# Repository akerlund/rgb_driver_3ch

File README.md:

# LED driver PCB, 3ch RGB

STM32F100 microcontroller with small SOT23 MOSFETs to drive 12V LED strips.
Four LEDs and two buttons for custom use.
Three potentiometers for controlling the light; HSL, i.e., Hue, Saturation and Light.
A CP2102 serial to USB interface.
Pinout for other peripherals, i.e., I2C, SPI and UART.

## Build

Using the ARM compiler (arm-none-eabi), which can be installed with

```
sudo apt-get install gcc-arm-none-eabi
```
then change directory and run the make file
```
cd code
make
```

## Program
I use Devilholk's verion of [stm32flash](https://github.com/devilholk/stm32flash),
with a cheap CP2102 USB to UART Bridge Controller.

### Programming sequence example

```
~/rgb_driver_3ch$ stm32flash -b 115200 -Rcs.rts -Bcs.dtr -w code/build/driver_rgb_3ch.bin /dev/ttyUSB0
stm32flash - http://stm32flash.googlecode.com/

Using Parser : Raw BINARY
Serial Config: 115200 8E1
Version      : 0x22
Option 1     : 0x00
Option 2     : 0x00
Device ID    : 0x0420 (Medium-density VL)
RAM          : 8KiB  (512b reserved by bootloader)
Flash        : 128KiB (sector size: 4x1024)
Option RAM   : 15b
System RAM   : 2KiB

Wrote address 0x08003304 (100.00%) Done.
```

### Pin configurations
Make sure you connect cables like this;

PCB | CP2102
-- | --
3.3V | N/C
GND | GND
TX | RXI
RX | TXO
RESET | RTS
BOOT | DTR

If you haven't, remember to add your username to the dialout group

```
sudo adduser <user_name> dialout
```

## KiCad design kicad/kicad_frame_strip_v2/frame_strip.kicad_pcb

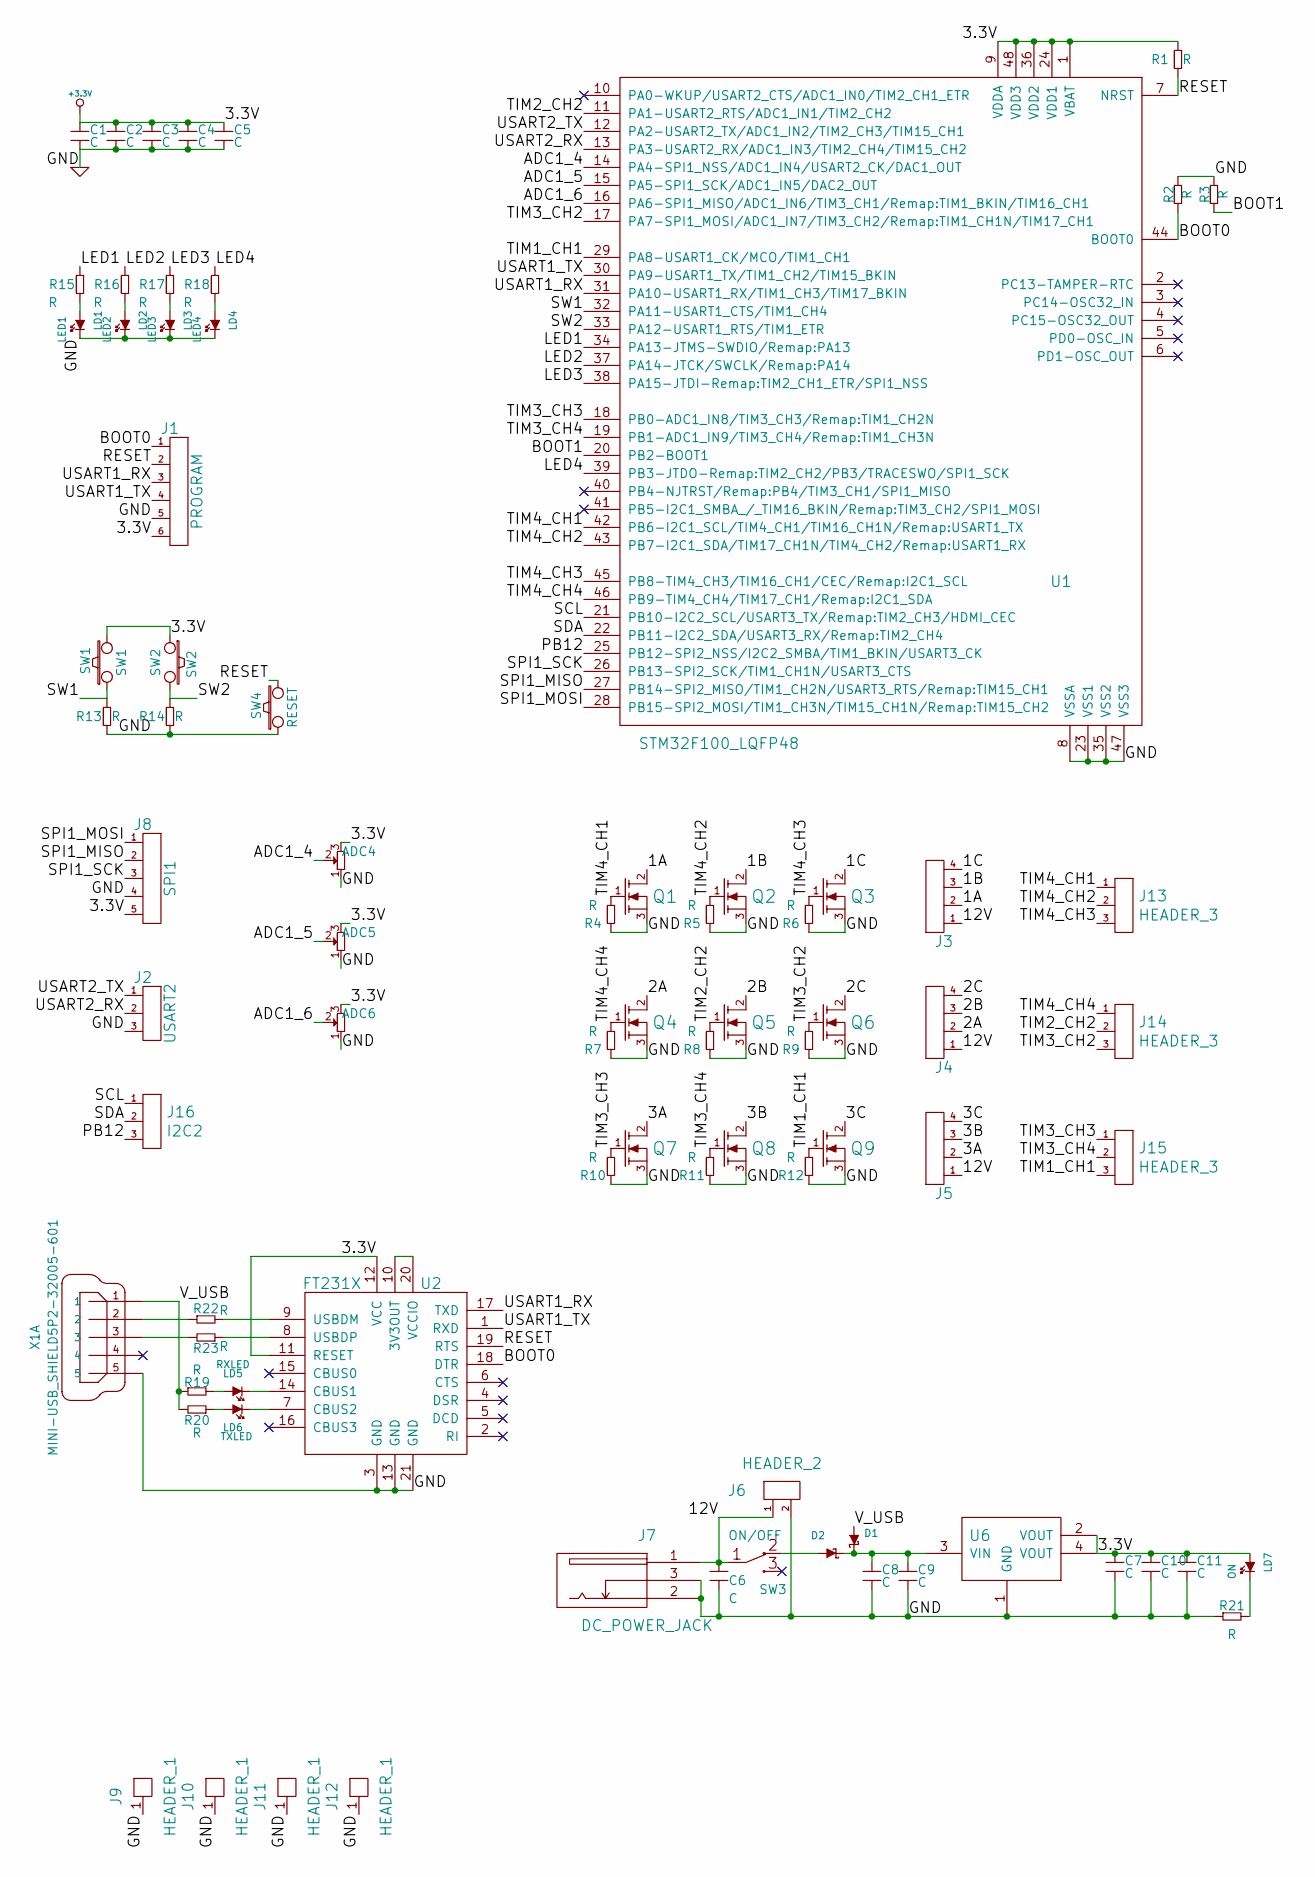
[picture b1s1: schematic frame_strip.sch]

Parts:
ADC4, ADC5, ADC6: POT; pin_socket_3
C1, C2, C3, C4, C5, C7, C8, C9, C10, C11: C; c_0603
C6: C; c_elec_5x5.3
D1, D2: SCHOTTKY; sod123
J1: PROGRAM; pin_strip_6
J2: USART2; pin_strip_3
J3, J4, J5: HEADER_4; pin_strip_4
J6: HEADER_2; pin_socket_2
J7: DC_POWER_JACK; dc_socket
J8: SPI1; pin_strip_5
J9, J10, J11, J12: HEADER_1; drill_2.0mm
J13, J14, J15: HEADER_3; pin_socket_3
J16: I2C2; pin_socket_3
LD1: LED1; Led_0805
LD2: LED2; Led_0805
LD3: LED3; Led_0805
LD4: LED4; Led_0805
LD5: RXLED; Led_0805
LD6: TXLED; Led_0805
LD7: ON; Led_0805
Q1, Q2, Q3, Q4, Q5, Q6, Q7, Q8, Q9: MOS_N_GDS; sot23
R1, R2, R3, R4, R5, R6, R7, R8, R9, R10, R11, R12, R13, R14, R15, R16, R17, R18, R19, R20, R21, R22, R23: R; r_0603
SW1: SW1; smd_push
SW2: SW2; smd_push
SW3: ON/OFF; switch_mmp122-r
SW4: RESET; smd_push
U1: STM32F100_LQFP48; lqfp48
U2: FT231X; qfn-20
U6: sot223
X1: MINI-USB_SHIELD5P2-32005-601; conn_usb_B_mini_smd

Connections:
+3.3V: ADC4.3, ADC5.3, ADC6.3, C1.1, C2.1, C3.1, C4.1, C5.1, C7.1, C10.1, C11.1, J1.6, J8.5, LD7.1 (A), R1.1, SW1.2, SW2.1, U1.1 (VBAT), U1.9 (VDDA), U1.24 (VDD1), U1.36 (VDD2), U1.48 (VDD3), U2.11 (RESET), U2.12 (VCC), U6.2 (VOUT), U6.4 (VOUT)
/1A: J3.2, Q1.2 (D)
/1B: J3.3, Q2.2 (D)
/1C: J3.4, Q3.2 (D)
/2A: J4.2, Q4.2 (D)
/2B: J4.3, Q5.2 (D)
/2C: J4.4, Q6.2 (D)
/3A: J5.2, Q7.2 (D)
/3B: J5.3, Q8.2 (D)
/3C: J5.4, Q9.2 (D)
/12V: C6.1, J3.1, J4.1, J5.1, J6.1, J7.1, SW3.1 (COM)
/ADC1_4: ADC4.2, U1.14 (PA4-SPI1_NSS/ADC1_IN4/USART2_CK/DAC1_OUT)
/ADC1_5: ADC5.2, U1.15 (PA5-SPI1_SCK/ADC1_IN5/DAC2_OUT)
/ADC1_6: ADC6.2, U1.16 (PA6-SPI1_MISO/ADC1_IN6/TIM3_CH1/Remap:T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)
/BOOT0: J1.1, R2.2, U1.44 (BOOT0), U2.18 (DTR)
/BOOT1: R3.2, U1.20 (PB2-BOOT1)
/LED1: R15.1, U1.34 (PA13-JTMS-SWDIO/Remap:PA13)
/LED2: R16.1, U1.37 (PA14-JTCK/SWCLK/Remap:PA14)
/LED3: R17.1, U1.38 (PA15-JTDI-Remap:TIM2_CH1_ETR/SPI1_NSS)
/LED4: R18.1, U1.39 (PB3-JTDO-Remap:TIM2_CH2/PB3/TRACESWO/SP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)
/PB12: J16.3, U1.25 (PB12-SPI2_NSS/I2C2_SMBA/TIM1_BKIN/USART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)
/RESET: J1.2, R1.2, SW4.2, U1.7 (NRST), U2.19 (RTS)
/SCL: J16.1, U1.21 (PB10-I2C2_SCL/USART3_TX/Remap:TIM2_CH3/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)
/SDA: J16.2, U1.22 (PB11-I2C2_SDA/USART3_RX/Remap:TIM2_CH4)
/SPI1_MISO: J8.2, U1.27 (PB14-SPI2_MISO/TIM1_CH2N/USART3_RTS/Rem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)
/SPI1_MOSI: J8.1, U1.28 (PB15-SPI2_MOSI/TIM1_CH3N/TIM15_CH1N/Rem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)
/SPI1_SCK: J8.3, U1.26 (PB13-SPI2_SCK/TIM1_CH1N/USART3_CTS)
/SW1: R13.1, SW1.1, U1.32 (PA11-USART1_CTS/TIM1_CH4)
/SW2: R14.1, SW2.2, U1.33 (PA12-USART1_RTS/TIM1_ETR)
/TIM1_CH1: J15.3, Q9.1 (G), R12.1, U1.29 (PA8-USART1_CK/MCO/TIM1_CH1)
/TIM2_CH2: J14.2, Q5.1 (G), R8.1, U1.11 (PA1-USART2_RTS/ADC1_IN1/TIM2_CH2)
/TIM3_CH2: J14.3, Q6.1 (G), R9.1, U1.17 (PA7-SPI1_MOSI/ADC1_IN7/TIM3_CH2/Remap:T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)
/TIM3_CH3: J15.1, Q7.1 (G), R10.1, U1.18 (PB0-ADC1_IN8/TIM3_CH3/Remap:TIM1_CH2N)
/TIM3_CH4: J15.2, Q8.1 (G), R11.1, U1.19 (PB1-ADC1_IN9/TIM3_CH4/Remap:TIM1_CH3N)
/TIM4_CH1: J13.1, Q1.1 (G), R4.1, U1.42 (PB6-I2C1_SCL/TIM4_CH1/TIM16_CH1N/Remap: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)
/TIM4_CH2: J13.2, Q2.1 (G), R5.1, U1.43 (PB7-I2C1_SDA/TIM17_CH1N/TIM4_CH2/Remap: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)
/TIM4_CH3: J13.3, Q3.1 (G), R6.1, U1.45 (PB8-TIM4_CH3/TIM16_CH1/CEC/Remap:I2C1_S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)
/TIM4_CH4: J14.1, Q4.1 (G), R7.1, U1.46 (PB9-TIM4_CH4/TIM17_CH1/Remap:I2C1_SDA)
/USART1_RX: J1.3, U1.31 (PA10-USART1_RX/TIM1_CH3/TIM17_BKIN), U2.17 (TXD)
/USART1_TX: J1.4, U1.30 (PA9-USART1_TX/TIM1_CH2/TIM15_BKIN), U2.1 (RXD)
/USART2_RX: J2.2, U1.13 (PA3-USART2_RX/ADC1_IN3/TIM2_CH4/TIM15_C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)
/USART2_TX: J2.1, U1.12 (PA2-USART2_TX/ADC1_IN2/TIM2_CH3/TIM15_C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)
/V_USB: D1.1 (A), R19.1, R20.2, X1.1
GND: ADC4.1, ADC5.1, ADC6.1, C1.2, C2.2, C3.2, C4.2, C5.2, C6.2, C7.2, C8.2, C9.2, C10.2, C11.2, J1.5, J2.3, J6.2, J7.2, J7.3, J8.4, J9.1, J10.1, J11.1, J12.1, LD1.2 (K), LD2.2 (K), LD3.2 (K), LD4.2 (K), Q1.3 (S), Q2.3 (S), Q3.3 (S), Q4.3 (S), Q5.3 (S), Q6.3 (S), Q7.3 (S), Q8.3 (S), Q9.3 (S), R2.1, R3.1, R4.2, R5.2, R6.2, R7.2, R8.2, R9.2, R10.2, R11.2, R12.2, R13.2, R14.2, R21.1, SW4.1, U1.8 (VSSA), U1.23 (VSS1), U1.35 (VSS2), U1.47 (VSS3), U2.3 (GND), U2.13 (GND), U2.21 (GND), U6.1 (GND), X1.5
unnamed: C8.1, C9.1, D1.2 (K), D2.2 (K), U6.3 (VIN)
unnamed: D2.1 (A), SW3.2 (NC)
unnamed: LD1.1 (A), R15.2
unnamed: LD2.1 (A), R16.2
unnamed: LD3.1 (A), R17.2
unnamed: LD4.1 (A), R18.2
unnamed: LD5.1 (A), R19.2
unnamed: LD5.2 (K), U2.14 (CBUS1)
unnamed: LD6.1 (A), R20.1
unnamed: LD6.2 (K), U2.7 (CBUS2)
unnamed: LD7.2 (K), R21.2
unnamed: R22.1, X1.2
unnamed: R22.2, U2.9 (USBDM)
unnamed: R23.1, U2.8 (USBDP)
unnamed: R23.2, X1.3
unnamed: U2.10 (3V3OUT), U2.20 (VCCIO)

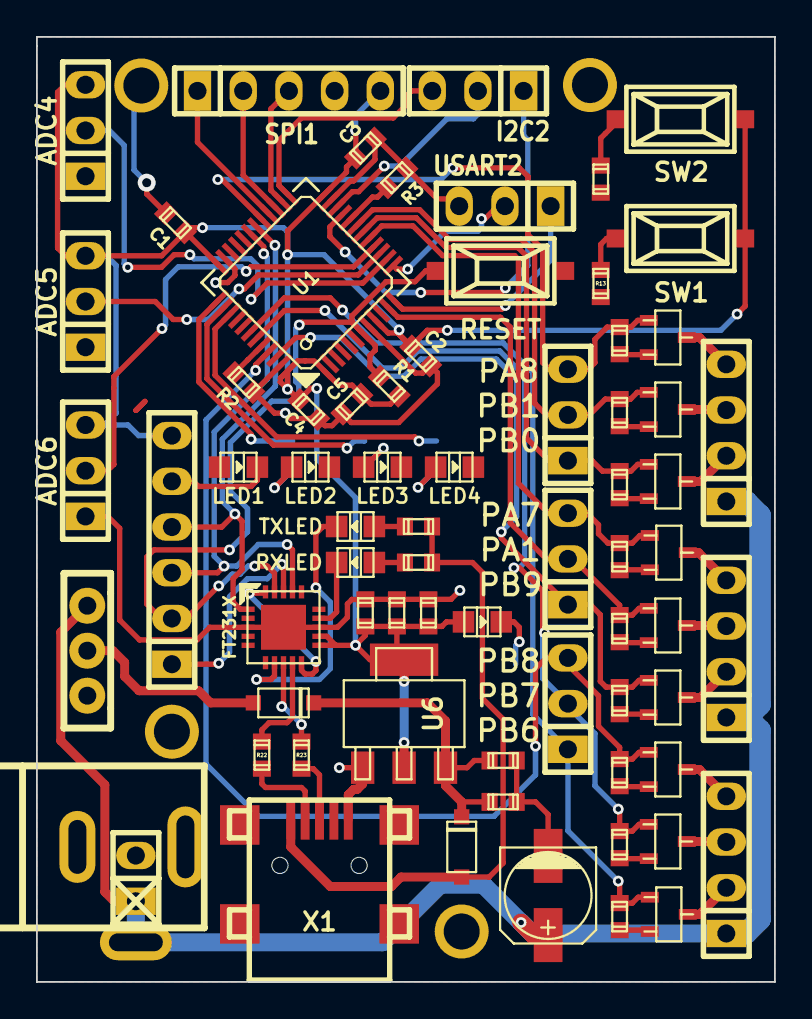
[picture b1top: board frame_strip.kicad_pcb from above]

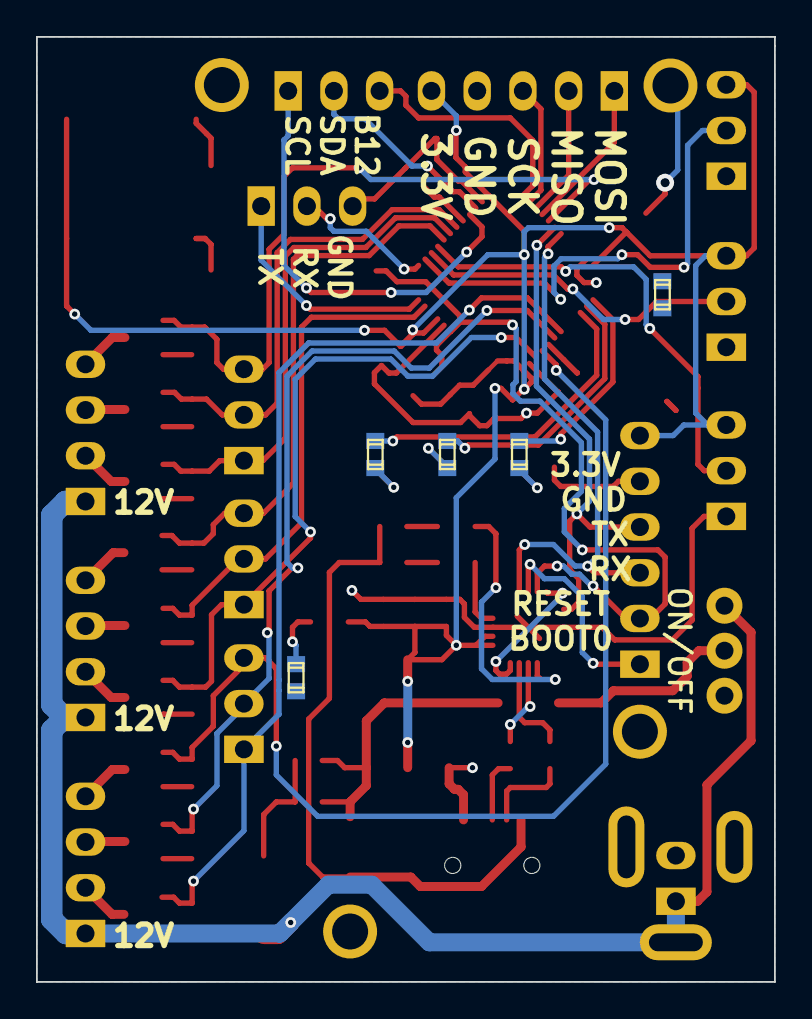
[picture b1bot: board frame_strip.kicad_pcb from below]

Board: 2 copper layers, 41.0 x 52.5 mm, 79 parts (5 on the bottom side), 60 nets.

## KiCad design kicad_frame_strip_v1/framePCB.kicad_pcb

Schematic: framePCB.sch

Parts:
C1: C; c_elec_8x6.5
C2, C4, C5, C6, C7: C; c_0603
D1: SETTING; Led_0603
D2: 1; Led_0603
D3: 3; Led_0603
D4, D5: 2; Led_0603
D6: 4; Led_0603
J1: dc_jack; dc_socket
J2: BOOT; smd_pin_5
J3: VIN/GRB0; smd_pin_4
J4: VIN/GRB1; smd_pin_4
J5: VIN/RGB2; smd_pin_4
J6: USART; smd_pin_3
J7: JST; pin_strip_2
J8: VDD; pin_strip_1
Q1, Q2, Q3, Q4, Q5, Q6, Q7, Q8, Q9: MOS_N_GDS; sot23
R1, R2, R3, R4, R5, R6, R7, R8, R9, R10, R11, R12, R13, R14, R15, R16, R17, R18, R19, R20: R; r_0603
RV1, RV2, RV3: POT; pot_eBay
SW2: BTN; smd_switch
SW3: TGL; smd_switch
SW4: ON/OFF; pin_socket_3
U1, U3, U4: drill; drill_2.0mm
U5: V_Reg_SOT; sot223
U6: STM32F100_LQFP48; lqfp48

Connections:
/12V: C1.1, J3.1, J4.1, J5.1, SW4.2 (NC), U5.3 (VIN)
/B1: J3.4, Q3.2 (D)
/B2: J4.4, Q6.2 (D)
/B3: J5.4, Q9.2 (D)
/BOOT0: J2.1, R1.2, U6.44 (BOOT0)
/BOOT1: R2.2, U6.20 (PB2-BOOT1)
/G1: J3.2, Q1.2 (D)
/G2: J4.2, Q4.2 (D)
/G3: J5.2, Q7.2 (D)
/POT1: RV1.2, U6.10 (PA0-WKUP/USART2_CTS/ADC1_IN0/TIM2_CH1_E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)
/POT2: RV2.2, U6.14 (PA4-SPI1_NSS/ADC1_IN4/USART2_CK/DAC1_OUT)
/POT3: RV3.2, U6.15 (PA5-SPI1_SCK/ADC1_IN5/DAC2_OUT)
/R1: J3.3, Q2.2 (D)
/R2: J4.3, Q5.2 (D)
/R3: J5.3, Q8.2 (D)
/RESET: J2.2, R3.2, U6.7 (NRST)
/SW1: R4.2, SW2.2
/SW2: R5.2, SW3.2
/TIM2_CH2: Q3.1 (G), R14.1, U6.11 (PA1-USART2_RTS/ADC1_IN1/TIM2_CH2)
/TIM2_CH3: Q4.1 (G), R15.1, U6.12 (PA2-USART2_TX/ADC1_IN2/TIM2_CH3/TIM15_C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)
/TIM2_CH4: Q5.1 (G), R16.1, U6.13 (PA3-USART2_RX/ADC1_IN3/TIM2_CH4/TIM15_C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)
/TIM3_CH1: Q6.1 (G), R17.1, U6.16 (PA6-SPI1_MISO/ADC1_IN6/TIM3_CH1/Remap:T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)
/TIM3_CH2: Q7.1 (G), R18.1, U6.17 (PA7-SPI1_MOSI/ADC1_IN7/TIM3_CH2/Remap:T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)
/TIM3_CH3: Q8.1 (G), R19.1, U6.18 (PB0-ADC1_IN8/TIM3_CH3/Remap:TIM1_CH2N)
/TIM3_CH4: Q9.1 (G), R20.1, U6.19 (PB1-ADC1_IN9/TIM3_CH4/Remap:TIM1_CH3N)
/TIM4_CH2: Q1.1 (G), R12.1, U6.43 (PB7-I2C1_SDA/TIM17_CH1N/TIM4_CH2/Remap: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)
/TIM4_CH3: Q2.1 (G), R13.1, U6.45 (PB8-TIM4_CH3/TIM16_CH1/CEC/Remap:I2C1_S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)
/USART1_RX: J2.3, U6.31 (PA10-USART1_RX/TIM1_CH3/TIM17_BKIN)
/USART1_TX: J2.4, U6.30 (PA9-USART1_TX/TIM1_CH2/TIM15_BKIN)
/USART3_RX: J6.2, U6.22 (PB11-I2C2_SDA/USART3_RX/Remap:TIM2_CH4)
/USART3_TX: J6.1, U6.21 (PB10-I2C2_SCL/USART3_TX/Remap:TIM2_CH3/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)
/VDD: C2.1, C4.1, C5.1, C6.1, C7.1, J8.1, R3.1, R4.1, R5.1, RV1.1, RV2.1, RV3.1, U5.2 (VOUT), U5.4 (VOUT), U6.1 (VBAT), U6.9 (VDDA), U6.24 (VDD1), U6.36 (VDD2), U6.48 (VDD3)
/seg_1: R6.1, U6.32 (PA11-USART1_CTS/TIM1_CH4)
/seg_2: R7.1, U6.34 (PA13-JTMS-SWDIO/Remap:PA13)
/seg_3: R8.1, U6.38 (PA15-JTDI-Remap:TIM2_CH1_ETR/SPI1_NSS)
/set_1: R9.1, U6.33 (PA12-USART1_RTS/TIM1_ETR)
/set_2: R10.1, U6.37 (PA14-JTCK/SWCLK/Remap:PA14)
/set_3: R11.1, U6.39 (PB3-JTDO-Remap:TIM2_CH2/PB3/TRACESWO/SP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)
GNDPWR: C1.2, C2.2, C4.2, C5.2, C6.2, C7.2, D1.2, D2.2, D3.2, D4.2, D5.2, D6.2, J1.1, J1.2, J2.5, J6.3, J7.2, Q1.3 (S), Q2.3 (S), Q3.3 (S), Q4.3 (S), Q5.3 (S), Q6.3 (S), Q7.3 (S), Q8.3 (S), Q9.3 (S), R1.1, R2.1, R12.2, R13.2, R14.2, R15.2, R16.2, R17.2, R18.2, R19.2, R20.2, RV1.3, RV2.3, RV3.3, SW2.1, SW3.1, U5.1 (GND), U6.8 (VSSA), U6.23 (VSS1), U6.35 (VSS2), U6.47 (VSS3)
unnamed: D1.1, R6.2
unnamed: D2.1, R7.2
unnamed: D3.1, R8.2
unnamed: D4.1, R9.2
unnamed: D5.1, R10.2
unnamed: D6.1, R11.2
unnamed: J1.3, J7.1, SW4.1 (COM)

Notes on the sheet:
One button for selectin RGB segment. One button for type of settings.
Shows selected segment.
Shows selected setting.
Speed. Phase. Color.
En lampa med alla lampor i den

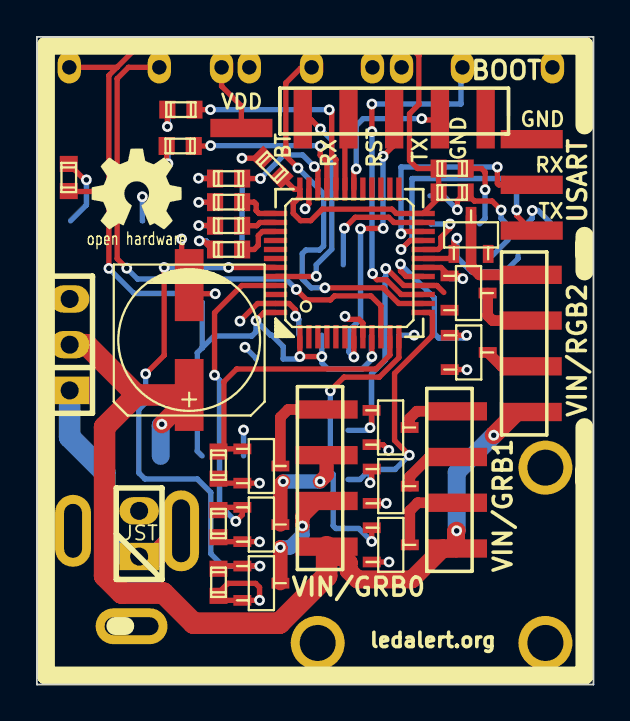
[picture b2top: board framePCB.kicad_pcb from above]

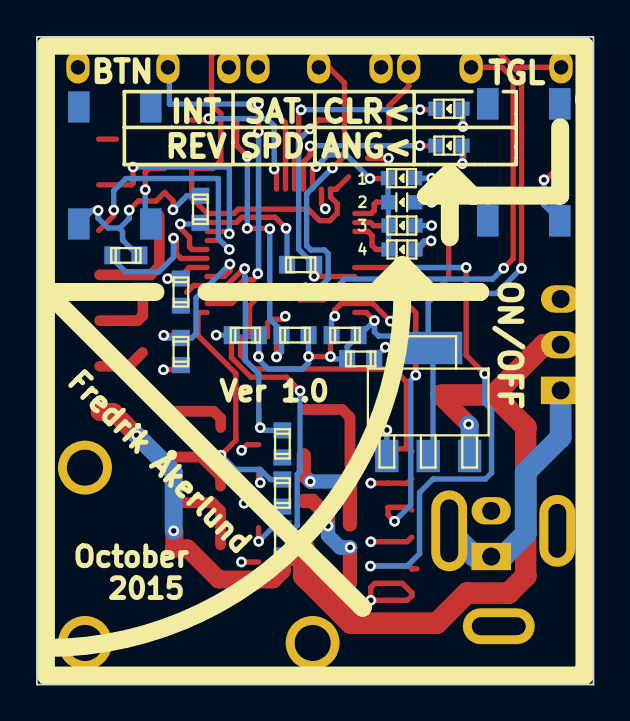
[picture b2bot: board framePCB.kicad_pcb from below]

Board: 2 copper layers, 30.9 x 36.0 mm, 60 parts (21 on the bottom side), 46 nets.

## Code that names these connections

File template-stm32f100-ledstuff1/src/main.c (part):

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
void setup_usart_1( ) {

	gpio_set_mode(GPIOA, GPIO_MODE_INPUT, GPIO_CNF_INPUT_FLOAT, GPIO_USART1_RX);


	usart_set_baudrate(USART1, 921600);
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
	// GPIO port A.
	gpio_set_mode(GPIOA, GPIO_MODE_OUTPUT_50_MHZ,
		      GPIO_CNF_OUTPUT_ALTFN_PUSHPULL, GPIO_USART2_TX);
	gpio_set_mode(GPIOA, GPIO_MODE_INPUT,
		      GPIO_CNF_INPUT_FLOAT, GPIO_USART2_RX);

	// UART parameters.
	usart_set_baudrate(USART2, 115200);
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
void setup_LEDs( ){

	// For using PA13-15 and PB3.
	gpio_primary_remap(AFIO_MAPR_SWJ_CFG_JTAG_OFF_SW_OFF,0);

	// JTAG GPIOs remapped.
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
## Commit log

2016-08-09 The new PCB
2016-08-09 gitignore
2016-08-09 After a build
2016-08-24 PCB, code
2016-09-28 Version 3 PCB
2016-10-07 The code for version 3
2016-10-08 The code for version 3.0
2017-01-14 Starts in AUTO, and something else
2019-12-26 Remove compiled files
2019-12-26 git ignore
2019-12-26 Renamed folder to code
2019-12-26 Created a KiCad folder
2019-12-26 PCB pictures
2019-12-26 Formatted main.c
2019-12-27 Croped pictures
2019-12-27 Makefile aligned
2019-12-27 Better readme
